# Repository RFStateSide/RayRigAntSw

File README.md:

# RayRigAntSw

RayRigAntSw is RF StateSide LLC's through-hole RF relay board for selecting two
rigs, three antennas and an amplifier/bypass path.

**Public Engineering Reference — AS-IS.** The editable design, BOM and
manufacturing files support study, independent construction, modification and
community improvement.

## Overview

Five 12 V SPDT relays provide RF routing through external low-side drivers. Two
PTT connections pass to the external controller. RaySspaController supplied the
drivers and sequencing used in our original integration test; another
controller can use the documented interface.

The original PCBWay boards were assembled and successfully tested. D1–D5 were
installed opposite the original PCB markings to obtain correct electrical
polarity. The supplied CAD includes the subsequent correction and was not
refabricated. See [assembly and history](docs/assembly-and-history.md).

## Hardware and Integration

Open [the KiCad 9 project](hardware/RayRigAntSw.kicad_pro). Required symbols
and footprints are included in project-local libraries. Optional 3D models are
not required or bundled.

The [integration guide](docs/integration.md) provides the eight-pin J8
interface, relay truth tables and external-driver requirements. The board does
not enforce transmitter arbitration or switching delays; those responsibilities
belong to the external controller.

[View schematic](docs/images/RayRigAntSw.svg) · [View PCB
front](docs/images/pcb-front.svg)

## Manufacturing and Assembly

Use the [BOM](bom/RayRigAntSw.csv) with the [P2-prep-01 manufacturing
set](manufacturing/README.md). This identifier ties the corrected sources to
their outputs; it does not identify a newly tested board. The original v2.0
silkscreen is retained.

Four inherited clearance findings, two J6 courtyard findings and nine schematic
ERC findings are documented in the [engineering
audit](PUBLIC_RELEASE_AUDIT.md). The supplied files are not represented as
DRC/ERC-clean. Assess the retained findings and component/mechanical
suitability before manufacture.

## Repository Contents

| Location | Contents |
|---|---|
| [hardware/](hardware/) | Editable KiCad project and local libraries |
| [bom/](bom/) | Component and procurement reference |
| [manufacturing/](manufacturing/) | Corrected Gerbers, drills and assembly references |
| [docs/](docs/) | Integration, assembly, limitations and provenance |
| [tools/](tools/) | Output generation and verification utilities |
| [PUBLIC_RELEASE_AUDIT.md](PUBLIC_RELEASE_AUDIT.md) | Attributed engineering verification evidence |

Original fabrication archives and internal review records are retained
separately. No parent firmware or development-repository history is included.

## Development Tools

KiCad was used for schematic capture and PCB design. Python utilities support
source verification and manufacturing-package integrity checks. Git and GitHub
are the intended version-control and distribution tools.

ChatGPT by OpenAI and OpenAI Codex assisted with engineering review,
documentation, source organization, validation and preparation of the
open-hardware reference. RF StateSide LLC performed the original hardware
design, assembly and historical integration testing.

## Known Limitations

No guaranteed RF power handling, isolation, insertion loss, frequency range,
hot-switching capability or certification is claimed. The corrected CAD has not
been physically refabricated. No future development or technical support is
promised. Read [known limitations](docs/known-limitations.md).

## License

Copyright RF StateSide LLC. Original project contributions are provided under
**CERN-OHL-P v2.0**, SPDX **CERN-OHL-P-2.0**. The unmodified [LICENSE](LICENSE)
is authoritative; retain [NOTICE](NOTICE) and applicable third-party notices.

See [licensing](docs/licensing.md) and [provenance](docs/provenance.md) for
scope and separately licensed material.

## Credits and Acknowledgments

RF StateSide LLC developed the original hardware and custom footprints. KiCad
library contributors supplied the upstream elements identified in the library
notices. Procurement references identify candidate parts and do not establish
the identity or fit of every historically installed component.

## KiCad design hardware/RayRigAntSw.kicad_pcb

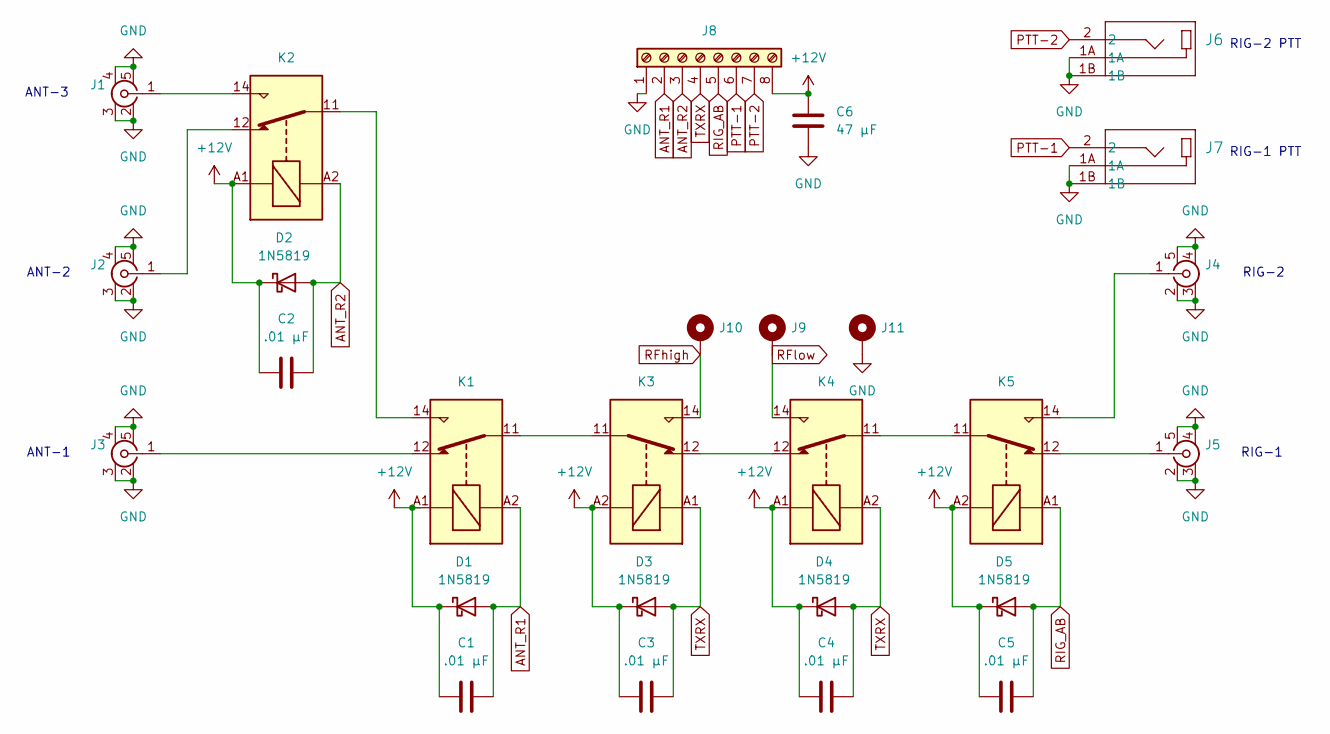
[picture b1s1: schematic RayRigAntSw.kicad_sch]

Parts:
C1, C2, C3, C4, C5: .01 µF; CAPRR500W50L730T250H650; MPN B32529C0103K289
C6: 47 µF; CAPRR500W50L730T250H650; MPN RDEC71E476MWK1H03B
D1, D2, D3, D4, D5: 1N5819; D_DO-41_SOD81_P10.16mm_Horizontal; MPN 1N5819-TP
J1, J2, J3, J4, J5: Conn_UHF; SO_239; MPN PE45478
J6, J7: RCJ-021; CUI_RCJ-021; MPN RCJ-021
J8: Screw_Terminal_01x08; TerminalBlock_Phoenix_MPT-0,5-8-2.54_1x08_P2.54mm_Horizontal; MPN OSTVN08A150
J9, J10: Hole_Pad; Conn_Tp1
J11: Hole_Pad; Conn_Pad_Tp
K1, K2, K3, K4, K5: G2RL-1-E; Relay_SPDT_Omron_G2RL-1-E; MPN G2RL-14-E DC12

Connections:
+12V: C1.1, C2.1, C3.1, C4.1, C5.1, C6.1, D1.1 (K), D2.1 (K), D3.1 (K), D4.1 (K), D5.1 (K), J8.8, K1.A1, K2.A1, K3.A2, K4.A1, K5.A2
ANT_R1: C1.2, D1.2 (A), J8.2, K1.A2
ANT_R2: C2.2, D2.2 (A), J8.3, K2.A2
GND: C6.2, J1.2, J1.3, J1.4, J1.5, J2.2, J2.3, J2.4, J2.5, J3.2, J3.3, J3.4, J3.5, J4.2, J4.3, J4.4, J4.5, J5.2, J5.3, J5.4, J5.5, J6.1A, J6.1B, J7.1A, J7.1B, J8.1, J11.1
unnamed: J1.1 (In), K2.14
unnamed: J2.1 (In), K2.12
unnamed: J3.1 (In), K1.12
unnamed: J4.1 (In), K5.14
unnamed: J5.1 (In), K5.12
unnamed: K1.11, K3.11
unnamed: K1.14, K2.11
unnamed: K3.12, K4.12
unnamed: K4.11, K5.11
PTT-1: J7.2, J8.6
PTT-2: J6.2, J8.7
RFhigh: J10.1, K3.14
RFlow: J9.1, K4.14
RIG_AB: C5.2, D5.2 (A), J8.5, K5.A1
TXRX: C3.2, C4.2, D3.2 (A), D4.2 (A), J8.4, K3.A1, K4.A2

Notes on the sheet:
RIG-1 PTT
ANT-2
RIG-1
ANT-3
RIG-2 PTT
RIG-2
ANT-1

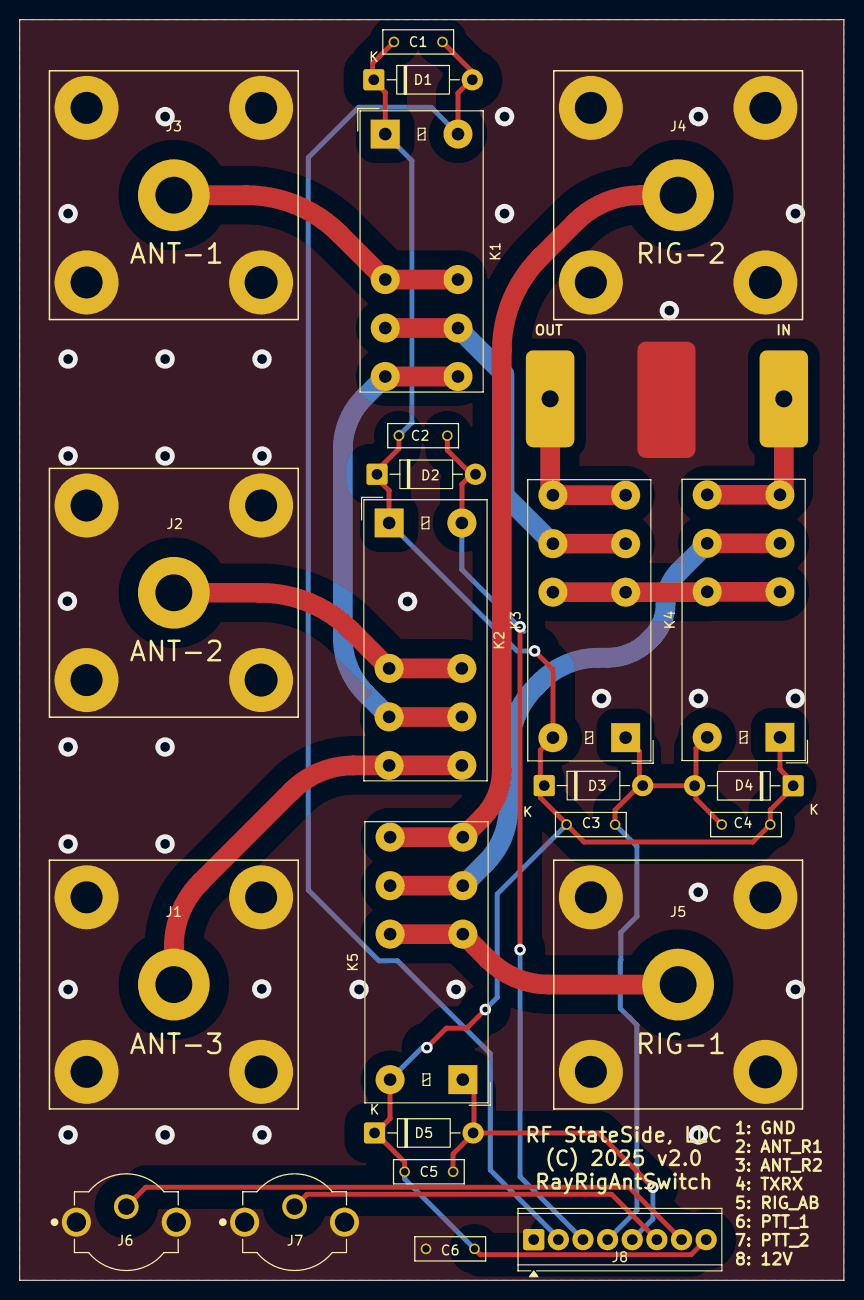
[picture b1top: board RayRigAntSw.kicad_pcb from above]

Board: 2 copper layers, 85.0 x 130.0 mm, 27 parts (0 on the bottom side), 19 nets.

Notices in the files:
hardware/RayRigAntSw.kicad_pcb:
(C) 2025 v2.0
